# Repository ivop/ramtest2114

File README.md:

# 2114 RAM Tester

The hardware is almost identical to [this](https://github.com/gpimblott/SRAM2114_Tester) project,
but the firmware is completely different and catches a lot of errors that would otherwise go
undetected.

### Hardware

Here's how to connect the 2114 to the Arduino Nano:

</img>

Click the image for a larger version, or view the [pdf version](doc/ramtest2114.pdf).
Connect the LEDs through a 390 ohm resistor to ground.
It's important to orient the LED [the right way](https://www.switchelectronics.co.uk/blogs/news/led-polarity-basic-guide).
The plus side goes to the Nano, the negative side to the resistor to ground.
To ease testing multiple 2114s it's advised to use a ZIF socket.

### Gerbers

</img>
</img>
</img>

In the [gerbers](kicad/gerbers) directory you'll find Gerber files for a complete PCB.
They have been tested to be working correctly.

### Flashing the firmware

Download [main.hex](https://github.com/ivop/ramtest2114/raw/refs/heads/master/main.hex) and use ```avrdude``` to flash it to the Arduino Nano.

```
avrdude -V -c arduino -b 57600 -P /dev/ttyUSB0 -p atmega328p -vv -U flash:w:main.hex
````

Replace ```/dev/ttyUSB0``` if your system is configured to assign a different serial device to your Nano.

### Usage

Insert a 2114 chip into the 18 pin socket and apply power to the Nano.
After booting it'll start testing immediately.
During the test, the red and green LEDs will blink.
When it's finished, either the green LED or the red LED stays on, indicating a success or a failure respectively.
Pressing the reset button on the Nano will rerun the test.
Be sure to disconnect the power when swapping the chip for another one to test.
Having the Vcc pin make contact without the ground pin being connected could damage the chip.

If you connect the Nano to the computer while testing, you can open a serial connection.
During the test, it'll print some diagnostic information, and a message when it's finished or encountered an error.

```
2114 SRAM MARCH MSS TESTER
^(w0)
^(r0,r0,w1,w1)
^(r1,r1,w0,w0)
...
...
v(r0,r0,w1,w1)
v(r1,r1,w0,w0)
v(r0)
RAM TESTED OK!
```

### Building the firmware from source

Install ```avr-gcc```, ```avr-libc```, and ```avrdude```.
Clone this repository and type ```make```.
Type ```make flash``` to automatically flash it to the connected Arduino Nano at ```/dev/ttyUSB0```.

### Algorithm

The tester uses the MARCH MSS algorithm.
It tests all combinations of the up/down (🡙) rules, and uses a set of three different background data value pairs to cover all errors it's able to detect.

Write errors:

* (W) SAF - Stuck At Fault
* (W) TF - Transition Fault
* (W) WDF - Write Destructive Fault
* (W) CFin - Inversion Coupling Fault
* (W) CFid - Idempotent Coupling Fault
* (W) CFst - Static Coupling Fault
* (W) CFds - Disturb Cell Coupling Fault
* (W) CFtr - Transition Coupling Fault
* (W) CFwd - Write Destructive Coupling

Read errors:

* (R) IRF - Incorrect Read Fault
* (R) RDF - Read Destructive Fault
* (R) DRDF - Deceptive Read Destructive Fault
* (R) SOF - Stuck Open Fault
* (R) ADF - Address Decoder Fault
* (R) CFds - Disturb Cell Coupling Fault
* (R) CFir - Incorrect Read Coupling Fault
* (R) CFrd - Read Destructive Coupling
* (R) CFir - Incorrect Read Coupling Fault

### References

* G. Harutunyan, V. A. Vardanian, and Y. Zorian, “Minimal march tests for unlinked static faults in random access memories,”
in 23rd IEEE VLSI Test Symposium (VTS’05), 2005, pp. 53–59, doi: 10.1109/VTS.2005.56.
[sci-hub link](https://sci-hub.se/10.1109/VTS.2005.56)
* [Understanding Memory Fault Models](https://www.embedded.com/understanding-memory-fault-models/)
( [archived version](https://web.archive.org/web/20240420233156/https://www.embedded.com/understanding-memory-fault-models/) )

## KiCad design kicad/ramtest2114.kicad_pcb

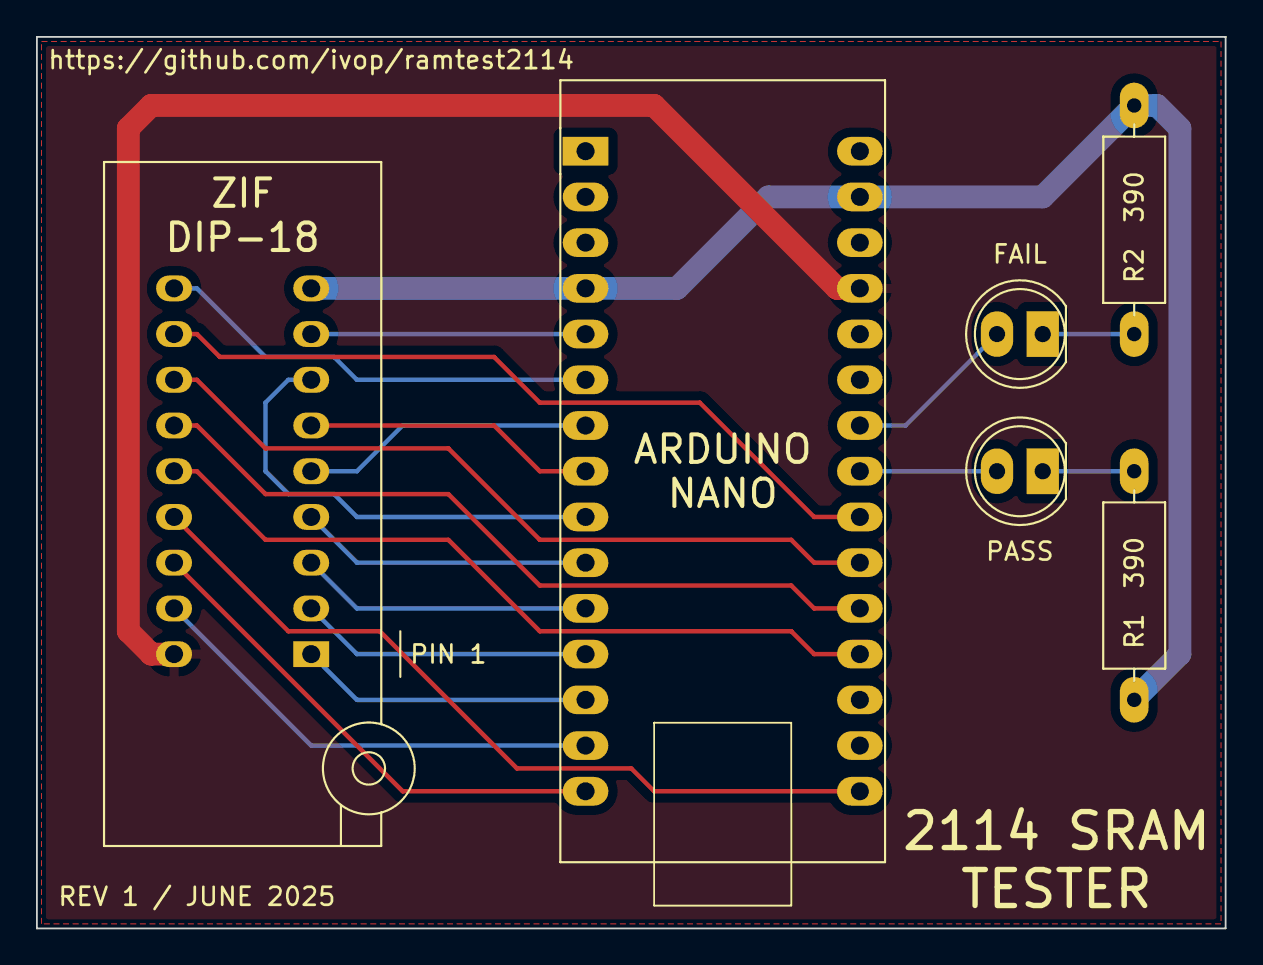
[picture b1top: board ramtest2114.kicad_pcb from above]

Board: 2 copper layers, 66.0 x 49.5 mm, 6 parts (0 on the bottom side), 22 nets.

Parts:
D1: PASS; LED_D5.0mm
D2: FAIL; LED_D5.0mm
R1, R2: 390; R_Axial_DIN0309_L9.0mm_D3.2mm_P12.70mm_Horizontal
U1: Arduino_Nano; Arduino Nano
U2: 2114; DIP_Socket-18_W4.3_W5.08_W7.62_W10.16_W10.9_3M_218-3341-00-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

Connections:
+5V: U1.27 (5V), U2.18 (Vcc)
/A0: U1.7 (PD4), U2.5 (A0)
/A1: U1.8 (PD5), U2.6 (A1)
/A2: U1.9 (PD6), U2.7 (A2)
/A3: U1.10 (PD7), U2.4 (A3)
/A4: U1.11 (PB0), U2.3 (A4)
/A5: U1.12 (PB1), U2.2 (A5)
/A6: U1.13 (PB2), U2.1 (A6)
/A7: U1.14 (PB3), U2.17 (A7)
/A8: U1.15 (PB4), U2.16 (A8)
/A9: U1.16 (PB5), U2.15 (A9)
/D0: U1.19 (PC0), U2.14 (D0)
/D1: U1.20 (PC1), U2.13 (D1)
/D2: U1.21 (PC2), U2.12 (D2)
/D3: U1.22 (PC3), U2.11 (D3)
/~CS: U1.5 (PD2), U2.8 (~CS)
/~WE: U1.6 (PD3), U2.10 (~WE)
GND: R1.2, R2.2, U1.4 (GND), U1.29 (GND), U2.9 (GND)
unnamed: D1.1 (K), R1.1
unnamed: D1.2 (A), U1.23 (PC4)
unnamed: D2.1 (K), R2.1
unnamed: D2.2 (A), U1.24 (PC5)

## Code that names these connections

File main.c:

// ramtest2114 - 2114 RAM tester
//
// MARCH (M)SS Algorithm
//
// Copyright © 2025 by Ivo van Poorten
// BSD 2-Clause License
// See LICENSE file for details
//
// MARCH MSS = { 🡙(w0); 🡑(r0,r0,w1,w1); 🡑(r1,r1,w0,w0); 🡓(r0,r0,w1,w1);
//               🡓(r1,r1,w0,w0); 🡙(r0) }
//
// Arduino Nano V3 (ATmega328 16MHz, 32kB Flash, 1kB ROM, 2kB RAM)
// Hardware similar to:
// https://github.com/gpimblott/SRAM2114_Tester
//
// PD2 = /CS
// PD3 = /WE
//
// PD4-PD7 = A0-A3
// PB0-PB5 = A4-A9
//
// PC0-PC3 = D0-D3
//
// PC4 green LED
// PC5 red LED


#include <stdio.h>
#include <stdint.h>
#include <avr/io.h>
#include <util/delay.h>

enum pins {
    PIN_CS    = 0b00000100,
    PIN_WE    = 0b00001000,
    PINS_DB   = 0b00001111,
    PINS_A0A3 = 0b11110000,
    PINS_A4A9 = 0b00111111,
    PIN_LEDG  = 0b00010000,
    PIN_LEDR  = 0b00100000,
    PINS_LEDS = 0b00110000
};

enum shifts {
    SHIFT_A0A3 = 4,
    SHIFT_A4A9 = 0
};

// ----------------------------------------------------------------------------

static void hw_usart_init(unsigned int ubrr) {
    UBRR0H = ubrr>>8;
    UBRR0L = ubrr;
    UCSR0B = 0;                             // disable all
    UCSR0B = _BV(RXEN0)  | _BV(TXEN0);      // enable RX and TX
    UCSR0C = _BV(UCSZ01) | _BV(UCSZ00);     // 8N1
//    UCSR0A = _BV(U2X0);                     // Double Speed
}

static void hw_usart_tx_byte(uint8_t byte) {
    while(!(UCSR0A & _BV(UDRE0))) ;         // wait for port ready to write
    UDR0 = byte;
}

static uint8_t hw_usart_rx_byte(void) {
    while(!(UCSR0A & _BV(RXC0))) ;          // wait for byte received
    return UDR0;
}

static void hw_usart_tx_block(const void *const buf, uint16_t len) {
    const uint8_t *b = buf;
    while (len--)
        hw_usart_tx_byte(*b++);
}

static void hw_usart_rx_block(void *const buf, uint16_t len) {
    uint8_t *b = buf;
    while (len--)
        *b++ = hw_usart_rx_byte();
}

static void hw_usart_tx_string(char *s) {
    while(*s) hw_usart_tx_byte(*s++);
}

// ----------------------------------------------------------------------------

static void led_green_on(void)  { PORTC |=  PIN_LEDG; };
static void led_green_off(void) { PORTC &= ~PIN_LEDG; };
static void led_red_on(void)    { PORTC |=  PIN_LEDR; };
static void led_red_off(void)   { PORTC &= ~PIN_LEDR; };

static inline void enable_cs(void)  { PORTD &= ~PIN_CS; }
static inline void disable_cs(void) { PORTD |=  PIN_CS; }
static inline void enable_we(void)  { PORTD &= ~PIN_WE; }
static inline void disable_we(void) { PORTD |=  PIN_WE; }

static inline void set_databus_output(void) { DDRC |=  PINS_DB; }
static inline void set_databus_input(void)  { DDRC &= ~PINS_DB; }

static void put_address_bus(uint16_t a) {
    PORTD &= ~PINS_A0A3;
    PORTD |= (a & 0x0f) << SHIFT_A0A3;
    PORTB &= ~PINS_A4A9;
    PORTB |= (a >> 4) << SHIFT_A4A9;
}

static void put_databus(uint8_t v) {
    PORTC &= ~PINS_DB;
    PORTC |= v & 0x0f;
}

static uint8_t get_databus(void) {
    return PINC & PINS_DB;
}

static uint8_t ram_read(uint16_t a) {
    put_address_bus(a);

    enable_cs();
    _delay_us(1);
    uint8_t v = get_databus();
    disable_cs();

    return v;
}

static void ram_write(uint16_t a, uint8_t v) {
    put_address_bus(a);

    set_databus_output();
    put_databus(v);

    enable_cs();
    enable_we();
    _delay_us(1);
    disable_we();
    disable_cs();

    set_databus_input();
}

// ----------------------------------------------------------------------------

static void fail(uint16_t a, uint8_t v, uint8_t e, int w) {
    hw_usart_tx_string("FAIL!\r\n");
    char s[128];
    snprintf(s, 128, "a=%03x, v=%1x, expected=%1x, line=%d\r\n", a, v, e, w);
    hw_usart_tx_string(s);
    led_green_off();
    led_red_on();
    while(1) ;
}

// ----------------------------------------------------------------------------

int main(void) {
    uint8_t updown = 0;         // bit 0 🡙(w0), bit 1 🡙(r0)
    uint8_t zero = 0b0000;
    uint8_t one = 0b1111;
    int a;
    uint8_t v;
    uint8_t bg_zero[3] = { 0b0000, 0b0011, 0b0101 };
    uint8_t bg_one[3]  = { 0b1111, 0b1100, 0b1010 };
    uint8_t bgidx = 0;

    hw_usart_init(103);         // 9600 baud, debug console

    DDRD |= 0b11111100;         // PD2-PD7 output   (/CS, /WE, A0-A3)
    DDRB |= 0b00111111;         // PB0-PB5 output   (A4-A9)
    DDRC |= PINS_LEDS;          // PC4-PC5 LEDs

    hw_usart_tx_string("2114 SRAM MARCH MSS TESTER\r\n");

    while (1) {

        if (!(updown &1)) {
            led_green_on();
            led_red_on();
        } else {
            led_green_off();
            led_red_off();
        }

        zero = bg_zero[bgidx];
        one  = bg_one[bgidx];

        // 🡙(w0)

        if (!(updown & 1)) {
            hw_usart_tx_string("^(w0)\r\n");
            for (a=0; a<1024; a++) {
                ram_write(a, zero);
            }
        } else {
            hw_usart_tx_string("v(w0)\r\n");
            for (a=1023; a>=0; a--) {
                ram_write(a, zero);
            }
        }

        // 🡑(r0,r0,w1,w1)

        hw_usart_tx_string("^(r0,r0,w1,w1)\r\n");
        for (a=0; a<1024; a++) {
            v = ram_read(a);
            if (v != zero) fail(a,v,zero,__LINE__);
            v = ram_read(a);
            if (v != zero) fail(a,v,zero,__LINE__);
            ram_write(a, one);
            ram_write(a, one);
        }

        // 🡑(r1,r1,w0,w0)

        hw_usart_tx_string("^(r1,r1,w0,w0)\r\n");
        for (int a=0; a<1024; a++) {
            v = ram_read(a);
            if (v != one) fail(a,v,one,__LINE__);
            v = ram_read(a);
            if (v != one) fail(a,v,one,__LINE__);
            ram_write(a, zero);
            ram_write(a, zero);
        }

        // 🡓(r0,r0,w1,w1)

        hw_usart_tx_string("v(r0,r0,w1,w1)\r\n");
        for (a=1023; a>=0; a--) {
            v = ram_read(a);
            if (v != zero) fail(a,v,zero,__LINE__);
            v = ram_read(a);
            if (v != zero) fail(a,v,zero,__LINE__);
            ram_write(a, one);
            ram_write(a, one);
        }

        // 🡓(r1,r1,w0,w0)

        hw_usart_tx_string("v(r1,r1,w0,w0)\r\n");
        for (int a=1023; a>=0; a--) {
            v = ram_read(a);
            if (v != one) fail(a,v,one,__LINE__);
            v = ram_read(a);
            if (v != one) fail(a,v,one,__LINE__);
            ram_write(a, zero);
            ram_write(a, zero);
        }

        // 🡙(r0)

        if (!(updown & 2)) {
            hw_usart_tx_string("^(r0)\r\n");
            for (a=0; a<1024; a++) {
                v = ram_read(a);
                if (v != zero) fail(a,v,zero,__LINE__);
            }
        } else {
            hw_usart_tx_string("v(r0)\r\n");
            for (a=1023; a>=0; a--) {
                v = ram_read(a);
                if (v != zero) fail(a,v,zero,__LINE__);
            }
        }

        updown++;
        if (updown == 4) {
            updown = 0;
            bgidx++;
            if (bgidx == 3) {
                hw_usart_tx_string("RAM TESTED OK!\r\n");
                led_green_on();
                led_red_off();
                while(1);
            }
        }
    }
}

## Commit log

2025-05-29 First commit.
2025-05-29 Add ods, pdf, and png
2025-05-29 Ignore some files, add main.hex firmware.
2025-06-02 Ignore stuff
2025-06-02 Add revision 1 of PCB.
2025-06-03 Update DRC pass
2025-06-14 Add images (KiCad render, plus an OK and a FAIL photo of real hardware)
